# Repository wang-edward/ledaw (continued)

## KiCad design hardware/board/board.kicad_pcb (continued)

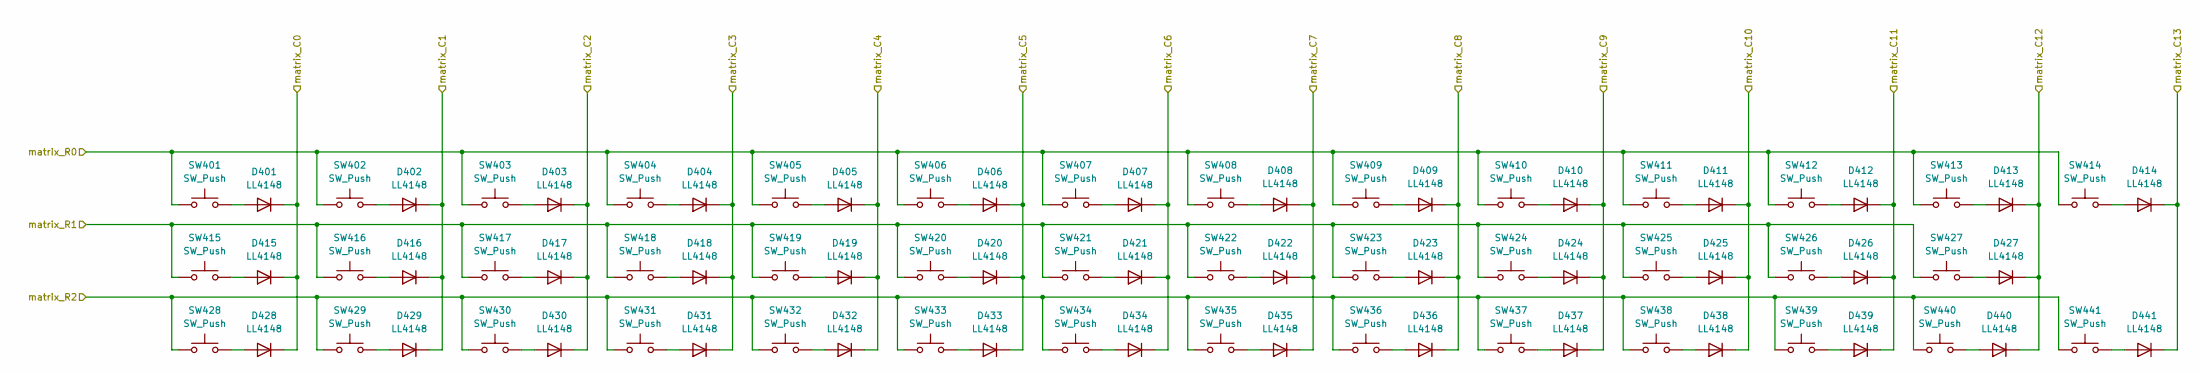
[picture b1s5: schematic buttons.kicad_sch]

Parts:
D401, D402, D403, D404, D405, D406, D407, D408, D409, D410, D411, D412, D413, D414, D415, D416, D417, D418, D419, D420, D421, D422, D423, D424, D425, D426, D427, D428, D429, D430, D431, D432, D433, D434, D435, D436, D437, D438, D439, D440, D441: LL4148; D_MiniMELF
SW401, SW402, SW403, SW404, SW405, SW406, SW407, SW408, SW409, SW410, SW411, SW412, SW413, SW414, SW415, SW416, SW417, SW418, SW419, SW420, SW421, SW422, SW423, SW424, SW425, SW426, SW427, SW428, SW429, SW430, SW431, SW432, SW433, SW434, SW435, SW436, SW437, SW438, SW439, SW440, SW441: SW_Push; ks-33-2.0

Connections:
/mcu/matrix_C0: D401.1 (K), D415.1 (K), D428.1 (K); also elsewhere on the board
/mcu/matrix_C1: D402.1 (K), D416.1 (K), D429.1 (K); also elsewhere on the board
/mcu/matrix_C2: D403.1 (K), D417.1 (K), D430.1 (K); also elsewhere on the board
/mcu/matrix_C3: D404.1 (K), D418.1 (K), D431.1 (K); also elsewhere on the board
/mcu/matrix_C4: D405.1 (K), D419.1 (K), D432.1 (K); also elsewhere on the board
/mcu/matrix_C5: D406.1 (K), D420.1 (K), D433.1 (K); also elsewhere on the board
/mcu/matrix_C6: D407.1 (K), D421.1 (K), D434.1 (K); also elsewhere on the board
/mcu/matrix_C7: D408.1 (K), D422.1 (K), D435.1 (K); also elsewhere on the board
/mcu/matrix_C8: D409.1 (K), D423.1 (K), D436.1 (K); also elsewhere on the board
/mcu/matrix_C9: D410.1 (K), D424.1 (K), D437.1 (K); also elsewhere on the board
/mcu/matrix_C10: D411.1 (K), D425.1 (K), D438.1 (K); also elsewhere on the board
/mcu/matrix_C11: D412.1 (K), D426.1 (K), D439.1 (K); also elsewhere on the board
/mcu/matrix_C12: D413.1 (K), D427.1 (K), D440.1 (K); also elsewhere on the board
/mcu/matrix_C13: D414.1 (K), D441.1 (K); also elsewhere on the board
/mcu/matrix_R0: SW401.1, SW402.1, SW403.1, SW404.1, SW405.1, SW406.1, SW407.1, SW408.1, SW409.1, SW410.1, SW411.1, SW412.1, SW413.1, SW414.1; also elsewhere on the board
/mcu/matrix_R1: SW415.1, SW416.1, SW417.1, SW418.1, SW419.1, SW420.1, SW421.1, SW422.1, SW423.1, SW424.1, SW425.1, SW426.1, SW427.1; also elsewhere on the board
/mcu/matrix_R2: SW428.1, SW429.1, SW430.1, SW431.1, SW432.1, SW433.1, SW434.1, SW435.1, SW436.1, SW437.1, SW438.1, SW439.1, SW440.1, SW441.1; also elsewhere on the board
unnamed: D401.2 (A), SW401.2
unnamed: D402.2 (A), SW402.2
unnamed: D403.2 (A), SW403.2
unnamed: D404.2 (A), SW404.2
unnamed: D405.2 (A), SW405.2
unnamed: D406.2 (A), SW406.2
unnamed: D407.2 (A), SW407.2
unnamed: D408.2 (A), SW408.2
unnamed: D409.2 (A), SW409.2
unnamed: D410.2 (A), SW410.2
unnamed: D411.2 (A), SW411.2
unnamed: D412.2 (A), SW412.2
unnamed: D413.2 (A), SW413.2
unnamed: D414.2 (A), SW414.2
unnamed: D415.2 (A), SW415.2
unnamed: D416.2 (A), SW416.2
unnamed: D417.2 (A), SW417.2
unnamed: D418.2 (A), SW418.2
unnamed: D419.2 (A), SW419.2
unnamed: D420.2 (A), SW420.2
unnamed: D421.2 (A), SW421.2
unnamed: D422.2 (A), SW422.2
unnamed: D423.2 (A), SW423.2
unnamed: D424.2 (A), SW424.2
unnamed: D425.2 (A), SW425.2
unnamed: D426.2 (A), SW426.2
unnamed: D427.2 (A), SW427.2
unnamed: D428.2 (A), SW428.2
unnamed: D429.2 (A), SW429.2
unnamed: D430.2 (A), SW430.2
unnamed: D431.2 (A), SW431.2
unnamed: D432.2 (A), SW432.2
unnamed: D433.2 (A), SW433.2
unnamed: D434.2 (A), SW434.2
unnamed: D435.2 (A), SW435.2
unnamed: D436.2 (A), SW436.2
unnamed: D437.2 (A), SW437.2
unnamed: D438.2 (A), SW438.2
unnamed: D439.2 (A), SW439.2
unnamed: D440.2 (A), SW440.2
unnamed: D441.2 (A), SW441.2

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
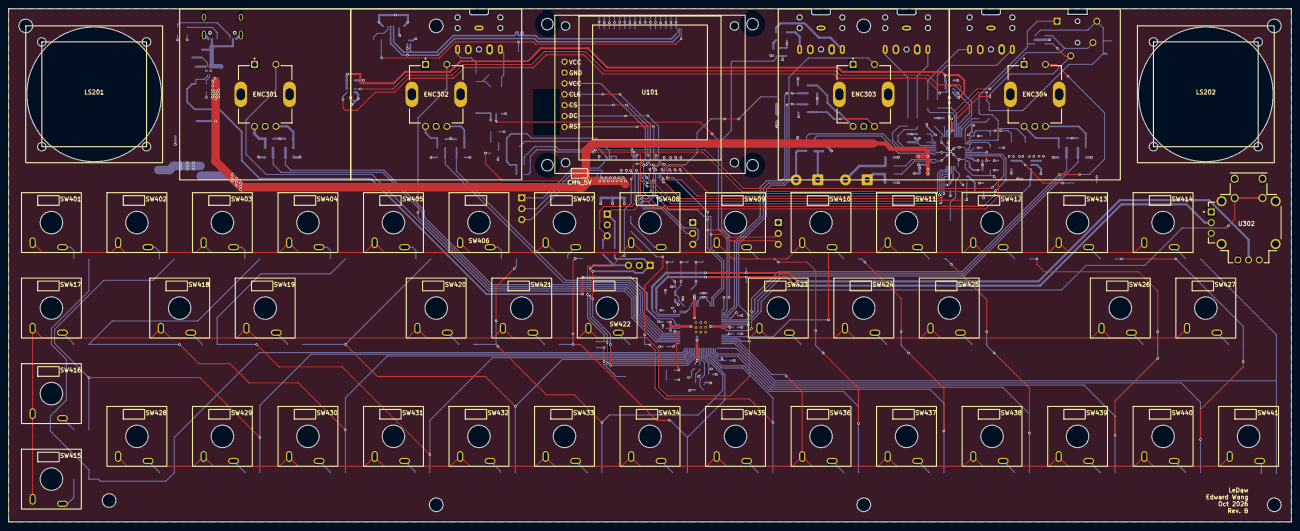
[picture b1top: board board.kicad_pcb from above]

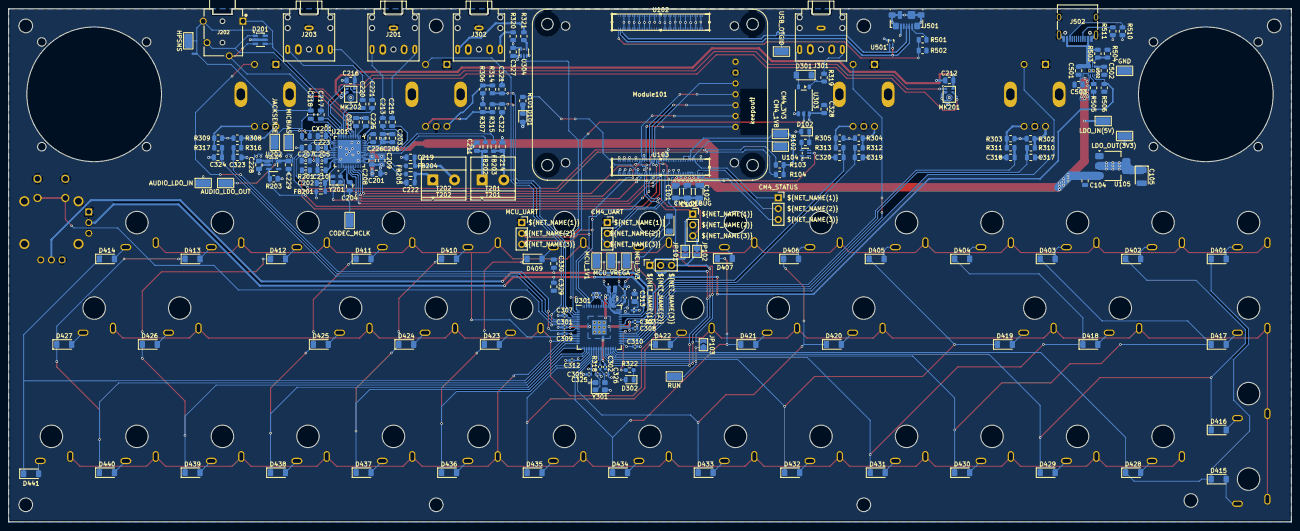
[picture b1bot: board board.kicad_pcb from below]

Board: 4 copper layers, 300.0 x 120.0 mm, 265 parts (207 on the bottom side), 179 nets.

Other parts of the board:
NT201: NetTie_2; NetTie-2_SMD_Pad0.5mm

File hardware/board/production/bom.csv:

Designator,Footprint,Quantity,Value,LCSC Part #
"C101, C102, C103",1206,3,22uF X5R 16V,C90146
C104,0805,1,"10 uF, 10 V, X7R ceramic",C380346
C105,CP_EIA-3528-21_Kemet-B,1,"10-22 µF, 10 V tantalum, ESR 0.033-2.2 Ω over operating conditions",C400102
"C201, C203, C213, C215, C313",0805,5,10uF,C1713
"C202, C204, C210, C212, C216, C327, C328, C329, C330, C501",0805,10,100nF,C49678
"C205, C206, C207, C208, C209, C217, C218, C220, C221, C223, C225, C226, C227, C228, C229, C503, CX201",0805,17,1uF,C376926
"C211, C214, C219, C222",0805,4,470pF,C1743
C224,0805,1,2.2uF,C377773
"C301, C303, C304, C305, C306, C307, C308, C309, C310, C311, C312",0402,11,100nF,C1525
"C302, C314, C315, C316",0402,4,4.7uF,C23733
"C317, C318, C319, C320, C321, C322, C323, C324",0805,8,10nF,C1710
"C325, C326",0402,2,15pF,C86285
C502,0805,1,3.3nF,C1738
D101,0805,1,LED Green,C2297
D102,0805,1,LED Red,C84256
D201,SOT-23-6,1,ESDA6V1BC6,C495220
"D301, D401, D402, D403, D404, D405, D406, D407, D408, D409, D410, D411, D412, D413, D414, D415, D416, D417, D418, D419, D420, D421, D422, D423, D424, D425, D426, D427, D428, D429, D430, D431, D432, D433, D434, D435, D436, D437, D438, D439, D440, D441",D_MiniMELF,42,LL4148,C78608
D302,0805,1,LED Blue,C965817
FB201,0805,1,600Ohm@100MHz,C341663
"FB202, FB203, FB204, FB205",0805,4,"600Ohm@100MHz, 1A",C41556732
J101,named_PinSocket_01x03,1,CM4_UART,C52016391
J102,named_PinSocket_01x03,1,CM4_DEBUG,C52016391
J103,named_PinSocket_01x03,1,MCU_DEBUG,C52016391
J104,named_PinSocket_01x03,1,MCU_UART,C52016391
J106,named_PinSocket_01x03,1,CM4_STATUS,C52016391
J202,CUI_SJ-43514,1,Headphone,C20182909
J501,USB_Micro-B_Molex_47346-0001,1,USB_B_Micro,C132560
J502,USB_C_Receptacle_HRO_TYPE-C-31-M-12,1,USB_C_Receptacle_PowerOnly_24P,C165948
JP103,SolderJumper-2_P1.3mm_Open_TrianglePad1.0x1.5mm,1,Jumper_SWCLK_Open,
L301,L_pol_2016,1,3.3uH,C42411119
MK201,Knowles_LGA-5_3.5x2.65mm,1,MicL,C2879853
MK202,Knowles_LGA-5_3.5x2.65mm,1,MicR,C2879853
MODULE101,Raspberry-Pi-4-Compute-Module,1,ComputeModule4-CM4,
"R101, R102",0805,2,1k,C17513
"R103, R104",0805,2,4.7k,C17673
"R201, R203, R302, R303, R304, R305, R306, R307, R308, R309, R310, R311, R312, R313, R314, R315, R316, R317, R505",0805,19,10k,C17414
R202,0805,1,2.2k,C17520
R301,0402,1,33,C138002
R318,0402,1,1k,C106235
R319,0805,1,220,C17557
R320,0805,1,33,C17634
R321,0805,1,10,C17415
R322,0603,1,1k,C22548
"R501, R502",0805,2,2.2K 1%,C17520
R503,0805,1,1M,C17514
R504,0805,1,390k,C17656
R506,0805,1,681 @ 1%,C17800
"R510, R511",0805,2,5.1k,C26023
T201,"TerminalBlock_Phoenix_MKDS-1,5-2-5.08_1x02_P5.08mm_Horizontal",1,TerminalL,C5183929
T202,"TerminalBlock_Phoenix_MKDS-1,5-2-5.08_1x02_P5.08mm_Horizontal",1,TerminalR,C5183929
TP101,named_TestPoint,1,LDO_IN(5V),
TP102,named_TestPoint,1,LDO_OUT(3V3),
TP103,named_TestPoint,1,CM4_5V,
TP104,named_TestPoint,1,CM4_3V3,
TP105,named_TestPoint,1,CM4_1V8,
TP106,named_TestPoint,1,GND,
TP107,named_TestPoint,1,RUN,
TP217,named_TestPoint,1,AUDIO_LDO_IN,
TP218,named_TestPoint,1,AUDIO_LDO_OUT,
TP301,named_TestPoint,1,MCU_3V3,
TP302,named_TestPoint,1,MCU_1V1,
TP303,named_TestPoint,1,MCU_VREGA,
TP502,named_TestPoint,1,USB_OTGID,
"U102, U103",dummy_hirose,2,~,C597931
U104,SOT-353_SC-70-5,1,74LVC1G07SE-7,C67531
U105,SOT-223-3_TabPin2,1,NCP1117-3.3_SOT223,C26537
U201,MAX98089ETN_T,1,MAX98089ETN_T,C2651816
U202,SOT-23-5,1,TPS7A2018PDBVR,C963430
U301,RP2350-QFN-80-1EP_10x10_P0.4mm_EP3.4x3.4mm_ThermalVias,1,RP2354B_80QFN,C39843328
U302,THB001P,1,THB001P,C2685355
U303,SO-5-6_4.55x3.7mm_P1.27mm,1,TLP2310,C7473281
U304,SOT-353_SC-70-5,1,74AHC1G125DCKR,C151890
U501,Texas_DRT-3,1,TPD2EUSB30,C97502
U502,SON50P200X200X80-9N,1,TPS259531DSGR,C2155674
Y201,Oscillator_SMD_SeikoEpson_SG210-4Pin_2.5x2.0mm,1,12.288MHz,C255992
Y301,Crystal_SMD_3225-4Pin_3.2x2.5mm,1,X322512MMB4SI,C50430

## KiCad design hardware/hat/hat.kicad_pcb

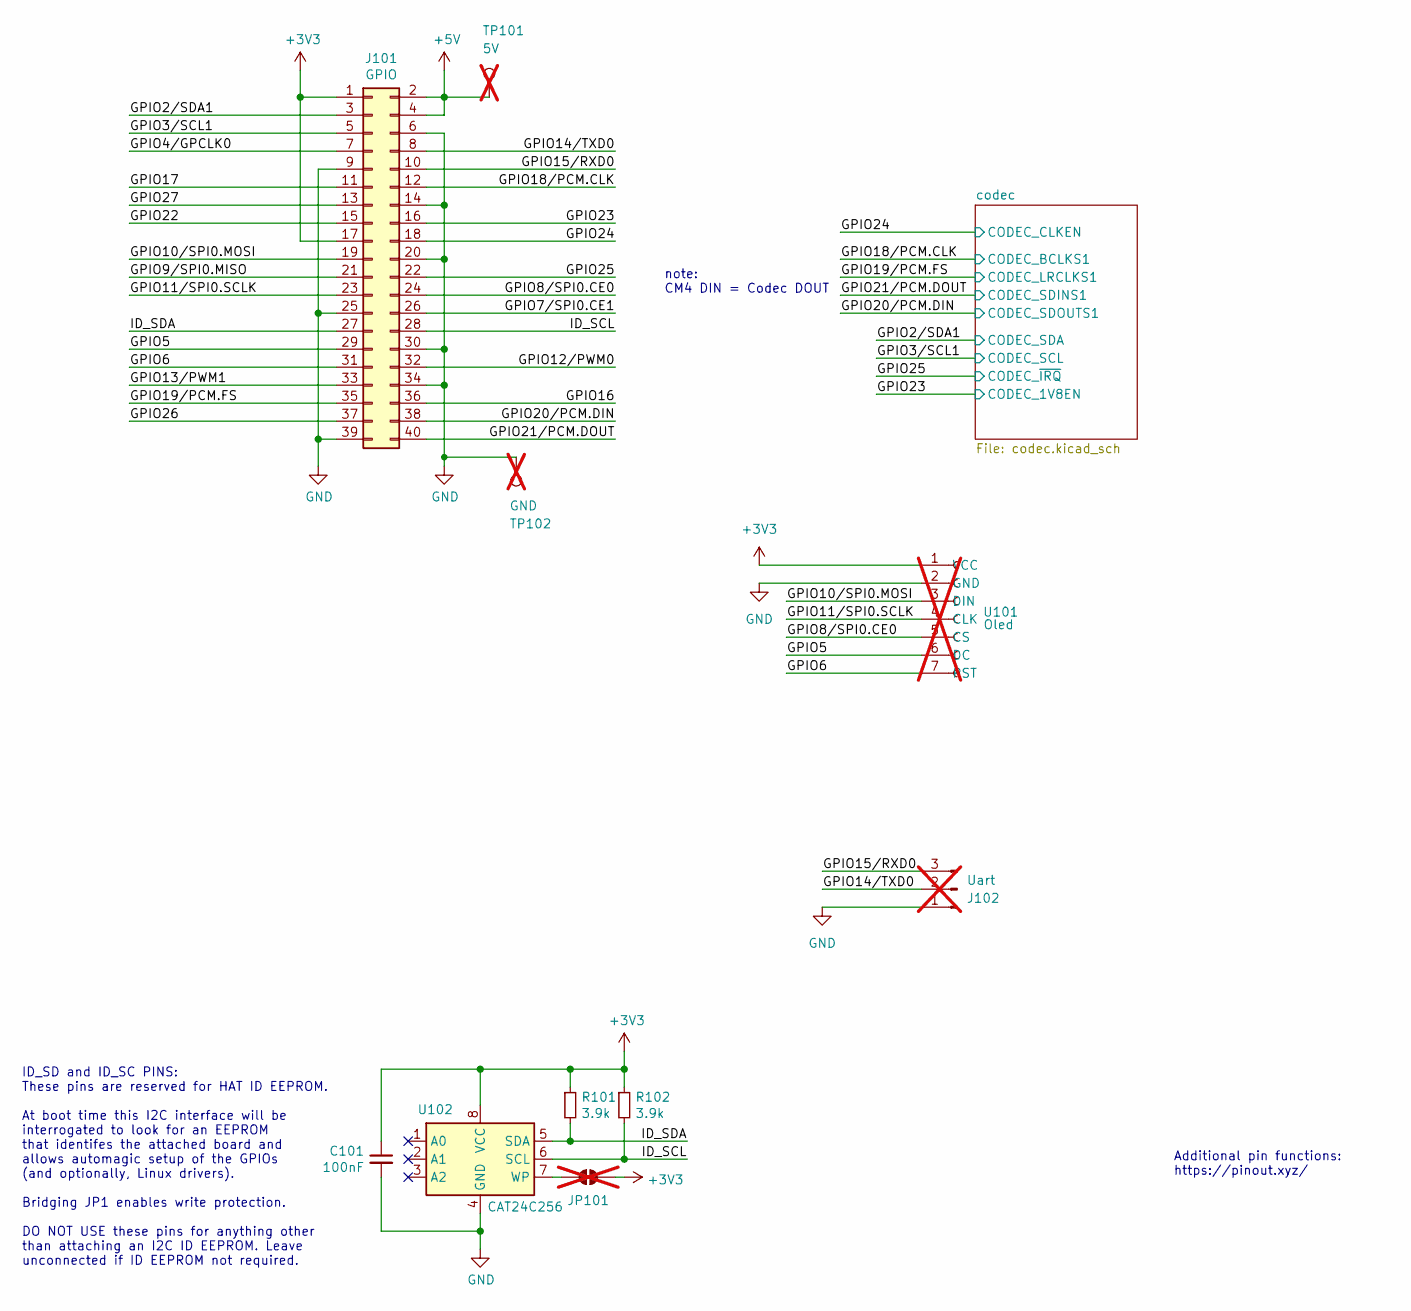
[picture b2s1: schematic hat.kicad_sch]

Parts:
C101: 100nF; C_0805_2012Metric; LCSC C49678
J101: GPIO; PinSocket_2x20_P2.54mm_Vertical; LCSC C2977589
J102: Uart; PinHeader_1x03_P2.54mm_Vertical; not fitted
JP101: ID_WP; SolderJumper-2_P1.3mm_Open_RoundedPad1.0x1.5mm; not fitted
R101, R102: 3.9k; R_0805_2012Metric; LCSC C17614
TP101: 5V; TestPoint_THTPad_1.5x1.5mm_Drill0.7mm; not fitted
TP102: GND; TestPoint_THTPad_1.5x1.5mm_Drill0.7mm; not fitted
U101: Oled; PinHeader_1x07_P2.54mm_Vertical; not fitted
U102: CAT24C256; SOIC-8_3.9x4.9mm_P1.27mm; LCSC C79987

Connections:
+3V3: C101.1, J101.1, J101.17, JP101.2 (B), R101.1, R102.1, U101.1 (VCC), U102.8 (VCC); also elsewhere on the board
+5V: J101.2, J101.4, TP101.1 (1_1); also elsewhere on the board
/GPIO2/SDA1: J101.3; also elsewhere on the board
/GPIO3/SCL1: J101.5; also elsewhere on the board
/GPIO4/GPCLK0: J101.7
/GPIO5: J101.29, U101.6 (DC)
/GPIO6: J101.31, U101.7 (RST)
/GPIO7/SPI0.CE1: J101.26
/GPIO8/SPI0.CE0: J101.24, U101.5 (CS)
/GPIO9/SPI0.MISO: J101.21
/GPIO10/SPI0.MOSI: J101.19, U101.3 (DIN)
/GPIO11/SPI0.SCLK: J101.23, U101.4 (CLK)
/GPIO12/PWM0: J101.32
/GPIO13/PWM1: J101.33
/GPIO14/TXD0: J101.8, J102.2
/GPIO15/RXD0: J101.10, J102.3
/GPIO16: J101.36
/GPIO17: J101.11
/GPIO18/PCM.CLK: J101.12; also elsewhere on the board
/GPIO19/PCM.FS: J101.35; also elsewhere on the board
/GPIO20/PCM.DIN: J101.38; also elsewhere on the board
/GPIO21/PCM.DOUT: J101.40; also elsewhere on the board
/GPIO22: J101.15
/GPIO23: J101.16; also elsewhere on the board
/GPIO24: J101.18; also elsewhere on the board
/GPIO25: J101.22; also elsewhere on the board
/GPIO26: J101.37
/GPIO27: J101.13
/ID_SCL: J101.28, R102.2, U102.6 (SCL)
/ID_SDA: J101.27, R101.2, U102.5 (SDA)
GND: C101.2, J101.6, J101.9, J101.14, J101.20, J101.25, J101.30, J101.34, J101.39, J102.1, TP102.1 (1_1), U101.2 (GND), U102.4 (GND); also elsewhere on the board
unnamed: JP101.1 (A), U102.7 (WP)

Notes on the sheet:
Additional pin functions: https://pinout.xyz/
ID_SD and ID_SC PINS: These pins are reserved for HAT ID EEPROM. At boot time this I2C interface will be interrogated to look for an EEPROM that identifes the attached board and allows automagic setup of the GPIOs (and optionally, Linux drivers). Bridging JP1 enables write protection. DO NOT USE th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
note: CM4 DIN = Codec DOUT

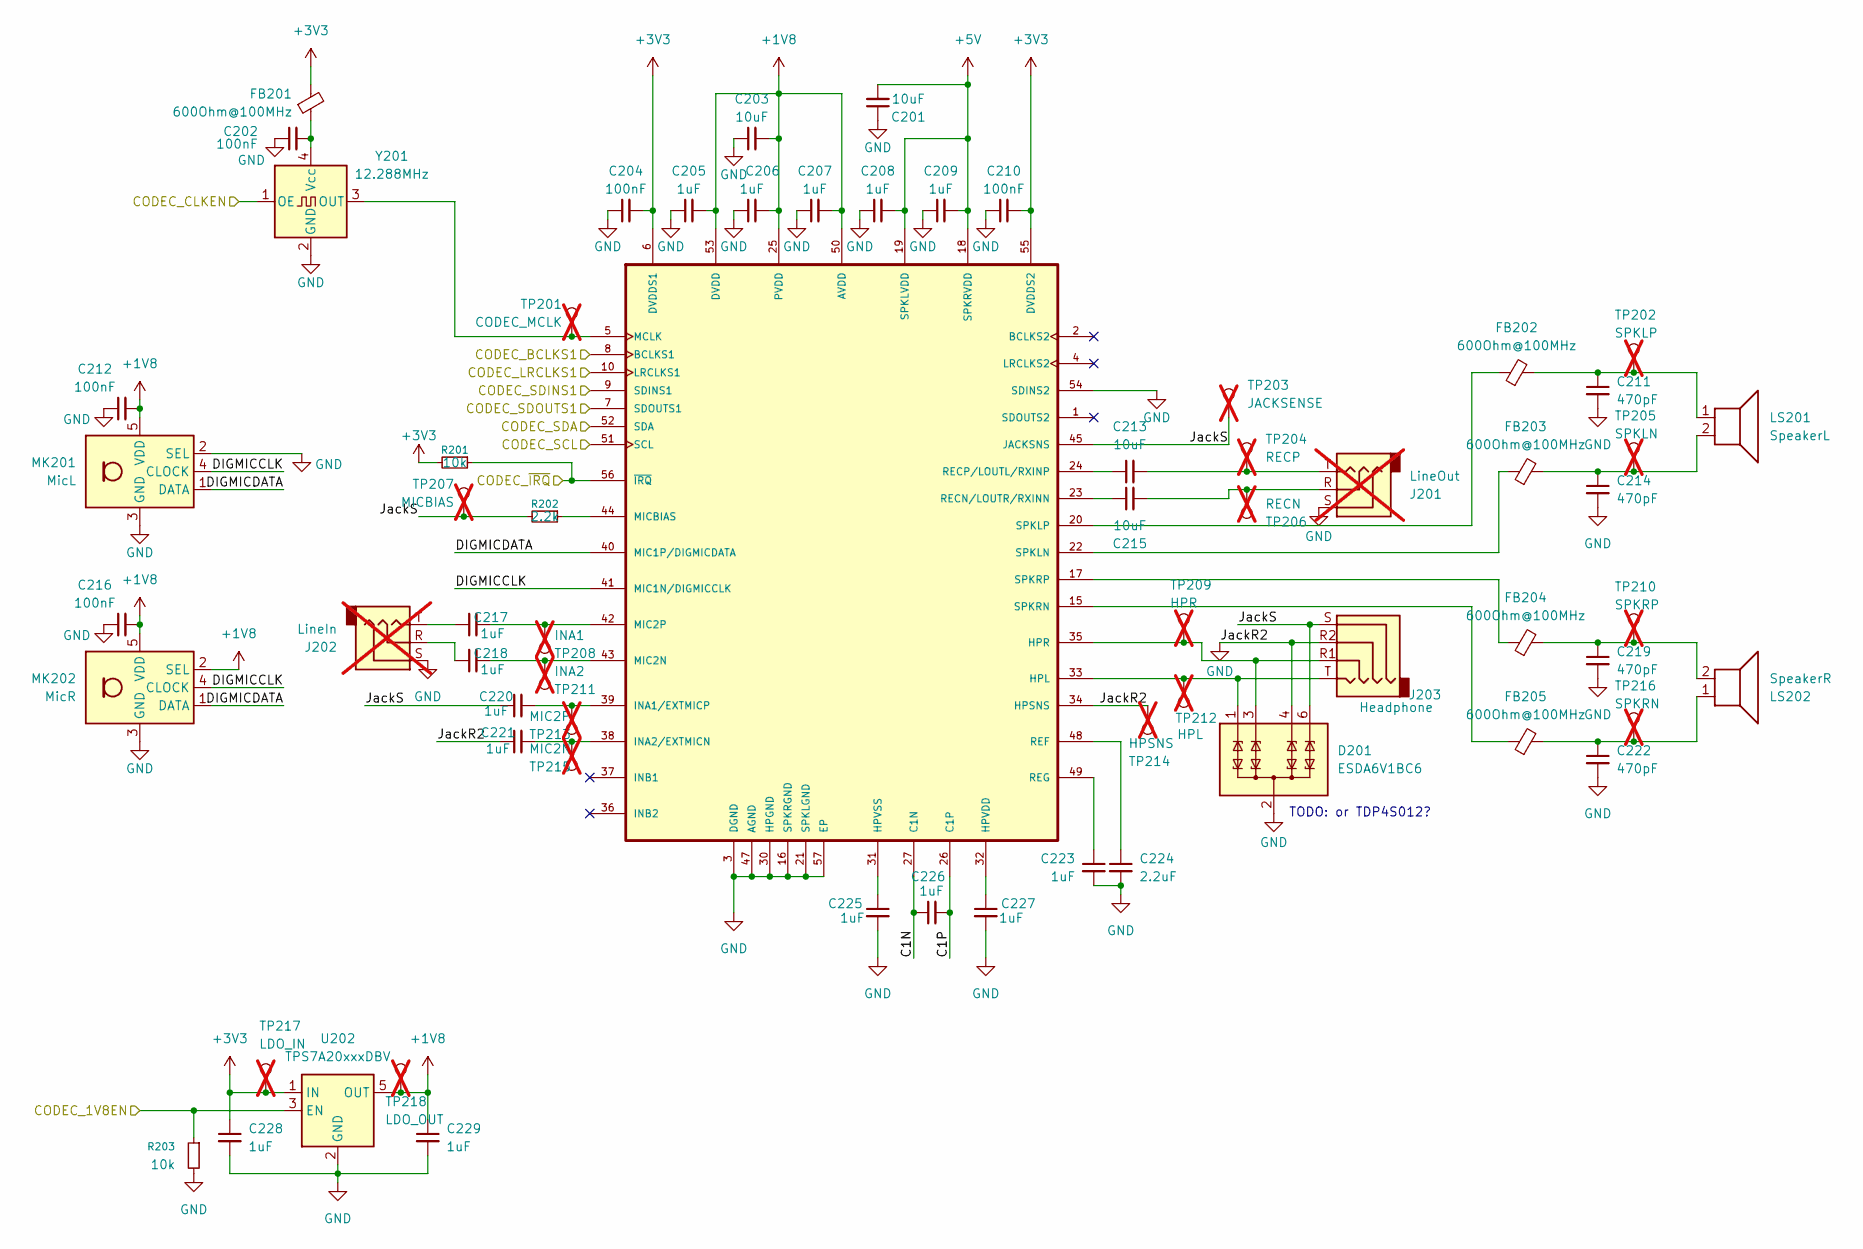
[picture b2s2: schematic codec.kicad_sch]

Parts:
C201, C203, C213, C215: 10uF; C_0805_2012Metric; LCSC C15850
C202, C204, C210, C212, C216: 100nF; C_0805_2012Metric; LCSC C49678
C205, C206, C207, C208, C209, C217, C218, C220, C221, C223, C225, C226, C227, C228, C229: 1uF; C_0805_2012Metric; LCSC C28323
C211, C214, C219, C222: 470pF; C_0805_2012Metric; LCSC C1743
C224: 2.2uF; C_0805_2012Metric; LCSC C377773
D201: ESDA6V1BC6; SOT-23-6; LCSC C495220
FB201, FB202, FB203, FB204, FB205: 600Ohm@100MHz; L_0805_2012Metric; LCSC C341663
J201: LineOut; Jack_3.5mm_CUI_SJ-3523-SMT_Horizontal; not fitted
J202: LineIn; Jack_3.5mm_CUI_SJ-3523-SMT_Horizontal; not fitted
J203: Headphone; CUI_SJ-43514-SMT-TR; LCSC C4992301
LS201: SpeakerL; TerminalBlock_Phoenix_MKDS-1,5-2-5.08_1x02_P5.08mm_Horizont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; LCSC C474881
LS202: SpeakerR; TerminalBlock_Phoenix_MKDS-1,5-2-5.08_1x02_P5.08mm_Horizont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; LCSC C474881
MK201: MicL; Knowles_LGA-5_3.5x2.65mm; LCSC C2879853
MK202: MicR; Knowles_LGA-5_3.5x2.65mm; LCSC C2879853
R201, R203: 10k; R_0805_2012Metric; LCSC C17414
R202: 2.2k; R_0805_2012Metric; LCSC C17520
TP201: CODEC_MCLK; TestPoint_Pad_D2.0mm; not fitted
TP202: SPKLP; TestPoint_Pad_D2.0mm; not fitted
TP203: JACKSENSE; TestPoint_Pad_D2.0mm; not fitted
TP204: RECP; TestPoint_Pad_D2.0mm; not fitted
TP205: SPKLN; TestPoint_Pad_D2.0mm; not fitted
TP206: RECN; TestPoint_Pad_D2.0mm; not fitted
TP207: MICBIAS; TestPoint_Pad_D2.0mm; not fitted
TP208: INA1; TestPoint_Pad_D2.0mm; not fitted
TP209: HPR; TestPoint_Pad_D2.0mm; not fitted
TP210: SPKRP; TestPoint_Pad_D2.0mm; not fitted
TP211: INA2; TestPoint_Pad_D2.0mm; not fitted
TP212: HPL; TestPoint_Pad_D2.0mm; not fitted
TP213: MIC2P; TestPoint_Pad_D2.0mm; not fitted
TP214: HPSNS; TestPoint_Pad_D2.0mm; not fitted
TP215: MIC2N; TestPoint_Pad_D2.0mm; not fitted
TP216: SPKRN; TestPoint_Pad_D2.0mm; not fitted
TP217: LDO_IN; TestPoint_Pad_D2.0mm; not fitted
TP218: LDO_OUT; TestPoint_Pad_D2.0mm; not fitted
U201: MAX98089ETN_T; LCSC C2651816
U202: TPS7A20xxxDBV; SOT-23-5; LCSC C2862740
Y201: 12.288MHz; Oscillator_SMD_SeikoEpson_SG210-4Pin_2.5x2.0mm; LCSC C20617595

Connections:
+1V8: C203.2, C205.2, C206.2, C207.2, C212.2, C216.2, C229.1, MK201.5 (VDD), MK202.2 (SEL), MK202.5 (VDD), TP218.1 (1_1), U201.25 (PVDD), U201.50 (AVDD), U201.53 (DVDD), U202.5 (OUT)
+3V3: C204.2, C210.2, C228.1, FB201.2, R201.2, TP217.1 (1_1), U201.6 (DVDDS1), U201.55 (DVDDS2), U202.1 (IN); also elsewhere on the board
+5V: C201.2, C208.2, C209.2, U201.18 (SPKRVDD), U201.19 (SPKLVDD); also elsewhere on the board
/GPIO2/SDA1: U201.52 (SDA); also elsewhere on the board
/GPIO3/SCL1: U201.51 (SCL); also elsewhere on the board
/GPIO18/PCM.CLK: U201.8 (BCLKS1); also elsewhere on the board
/GPIO19/PCM.FS: U201.10 (LRCLKS1); also elsewhere on the board
/GPIO20/PCM.DIN: U201.7 (SDOUTS1); also elsewhere on the board
/GPIO21/PCM.DOUT: U201.9 (SDINS1); also elsewhere on the board
/GPIO23: R203.1, U202.3 (EN); also elsewhere on the board
/GPIO24: Y201.1 (OE); also elsewhere on the board
/GPIO25: R201.1, U201.56 (~IRQ); also elsewhere on the board
/codec/C1N: C226.1, U201.27 (C1N)
/codec/C1P: C226.2, U201.26 (C1P)
/codec/DIGMICCLK: MK201.4 (CLOCK), MK202.4 (CLOCK), U201.41 (MIC1N/DIGMICCLK)
/codec/DIGMICDATA: MK201.1 (DATA), MK202.1 (DATA), U201.40 (MIC1P/DIGMICDATA)
/codec/JackS: C220.1, D201.6 (TVS4), J203.S, R202.2, TP203.1 (1_1), TP207.1 (1_1), U201.45 (JACKSNS)
GND: C201.1, C202.1, C203.1, C204.1, C205.1, C206.1, C207.1, C208.1, C209.1, C210.1, C211.2, C212.1, C214.2, C216.1, C219.2, C221.1, C222.2, C223.2, C224.2, C225.2, C227.2, C228.2, C229.2, D201.2 (COM), D201.4 (TVS3), D201.5 (COM), J201.S, J202.S, J203.R2, MK201.2 (SEL), MK201.3 (GND), MK202.3 (GND), R203.2, TP214.1 (1_1), U201.3 (DGND), U201.16 (SPKRGND), U201.21 (SPKLGND), U201.30 (HPGND), U201.34 (HPSNS), U201.47 (AGND), U201.54 (SDINS2), U201.57 (EP), U202.2 (GND), Y201.2 (GND); also elsewhere on the board
unnamed: C211.1, FB202.2, LS201.1, TP202.1 (1_1)
unnamed: C213.2, J201.T, TP204.1 (1_1)
unnamed: C214.1, FB203.2, LS201.2, TP205.1 (1_1)
unnamed: C215.2, J201.R, TP206.1 (1_1)
unnamed: C217.1, J202.T
unnamed: C218.1, J202.R
unnamed: C219.1, FB204.2, LS202.2, TP210.1 (1_1)
unnamed: C222.1, FB205.2, LS202.1, TP216.1 (1_1)
unnamed: D201.1 (TVS1), J203.T, TP212.1 (1_1), U201.33 (HPL)
unnamed: D201.3 (TVS2), J203.R1, TP209.1 (1_1), U201.35 (HPR)
unnamed: C227.1, U201.32 (HPVDD)
unnamed: C225.1, U201.31 (HPVSS)
unnamed: C220.2, TP213.1 (1_1), U201.39 (INA1/EXTMICP)
unnamed: C221.2, TP215.1 (1_1), U201.38 (INA2/EXTMICN)
unnamed: TP201.1 (1_1), U201.5 (MCLK), Y201.3 (OUT)
unnamed: C218.2, TP211.1 (1_1), U201.43 (MIC2N)
unnamed: C217.2, TP208.1 (1_1), U201.42 (MIC2P)
unnamed: R202.1, U201.44 (MICBIAS)
unnamed: C215.1, U201.23 (RECN/LOUTR/RXINN)
unnamed: C213.1, U201.24 (RECP/LOUTL/RXINP)
unnamed: C224.1, U201.48 (REF)
unnamed: C223.1, U201.49 (REG)
unnamed: FB203.1, U201.22 (SPKLN)
unnamed: FB202.1, U201.20 (SPKLP)
unnamed: FB205.1, U201.15 (SPKRN)
unnamed: FB204.1, U201.17 (SPKRP)
unnamed: C202.2, FB201.1, Y201.4 (Vcc)

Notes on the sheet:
TODO: or TDP4S012?

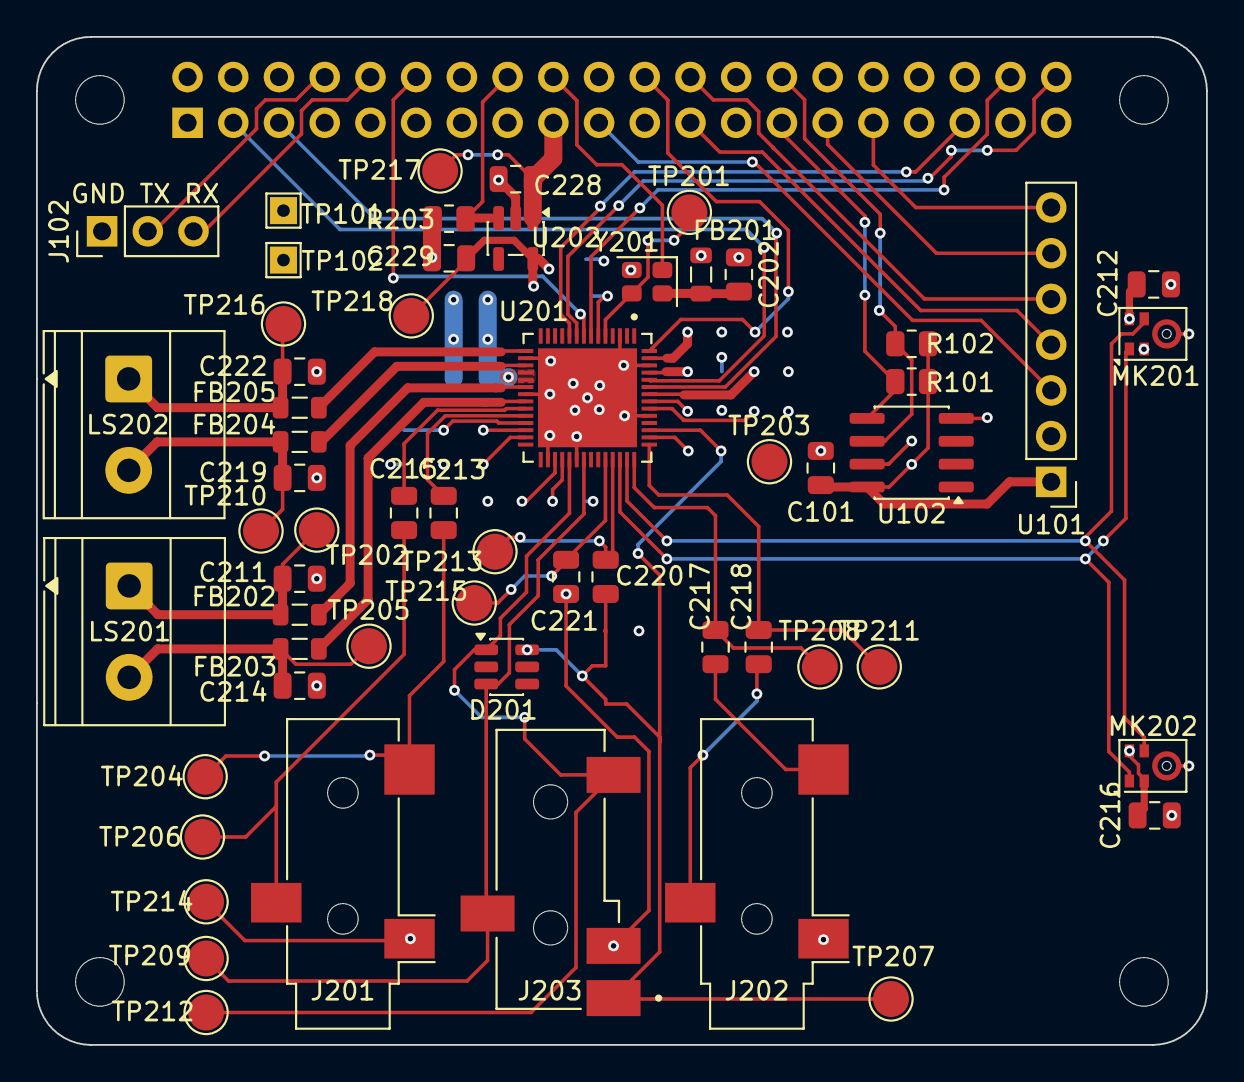
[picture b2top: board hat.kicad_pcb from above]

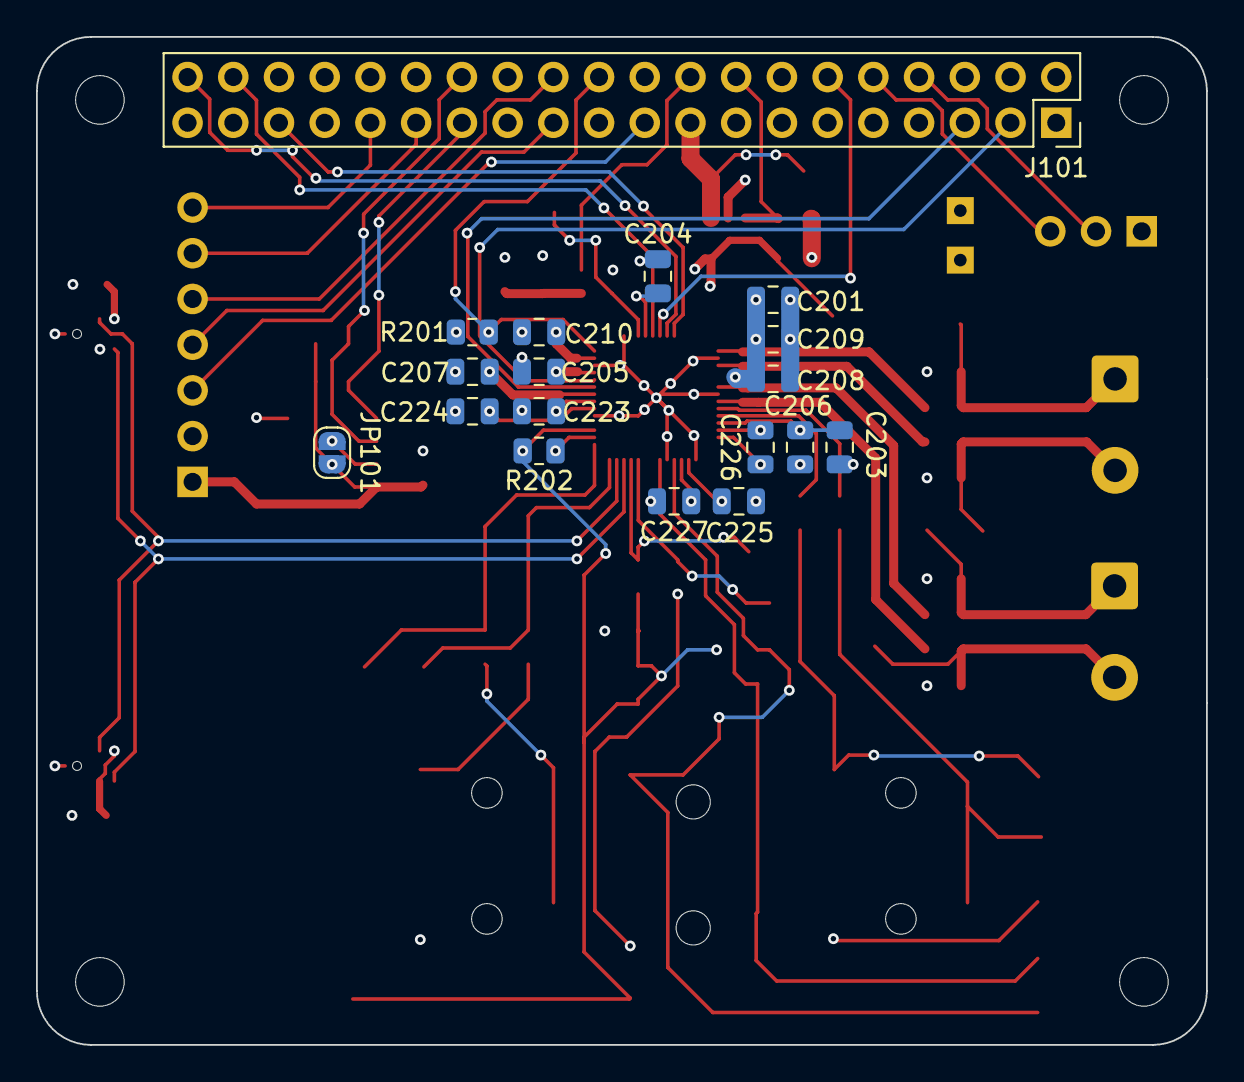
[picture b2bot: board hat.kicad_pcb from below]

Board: 4 copper layers, 65.0 x 56.0 mm, 80 parts (18 on the bottom side), 55 nets.

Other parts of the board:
MH1, MH2, MH3, MH4: MountingHole_2.7mm_M2.5
